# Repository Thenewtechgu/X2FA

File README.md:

# X2FA

X2FA is an open-source FIDO2 2fa key.

- What's a 2fa key

A 2FA key is a small device that adds extra security to logins by requiring both your password and the physical key. It uses secure encryption (like FIDO2 or NFC) to verify your identity and protect against hacks.

- What's FIDO2?

FIDO2 is a secure authentication standard that replaces passwords with cryptographic keys. It uses a hardware device (like a USB or NFC key) to prove your identity by signing a challenge from the website. This keeps your credentials safe and makes phishing attacks nearly impossible.

Basically, 2XFA makes it harder for hackers to hack you

Source code: Coming soon

Bill of Materials:

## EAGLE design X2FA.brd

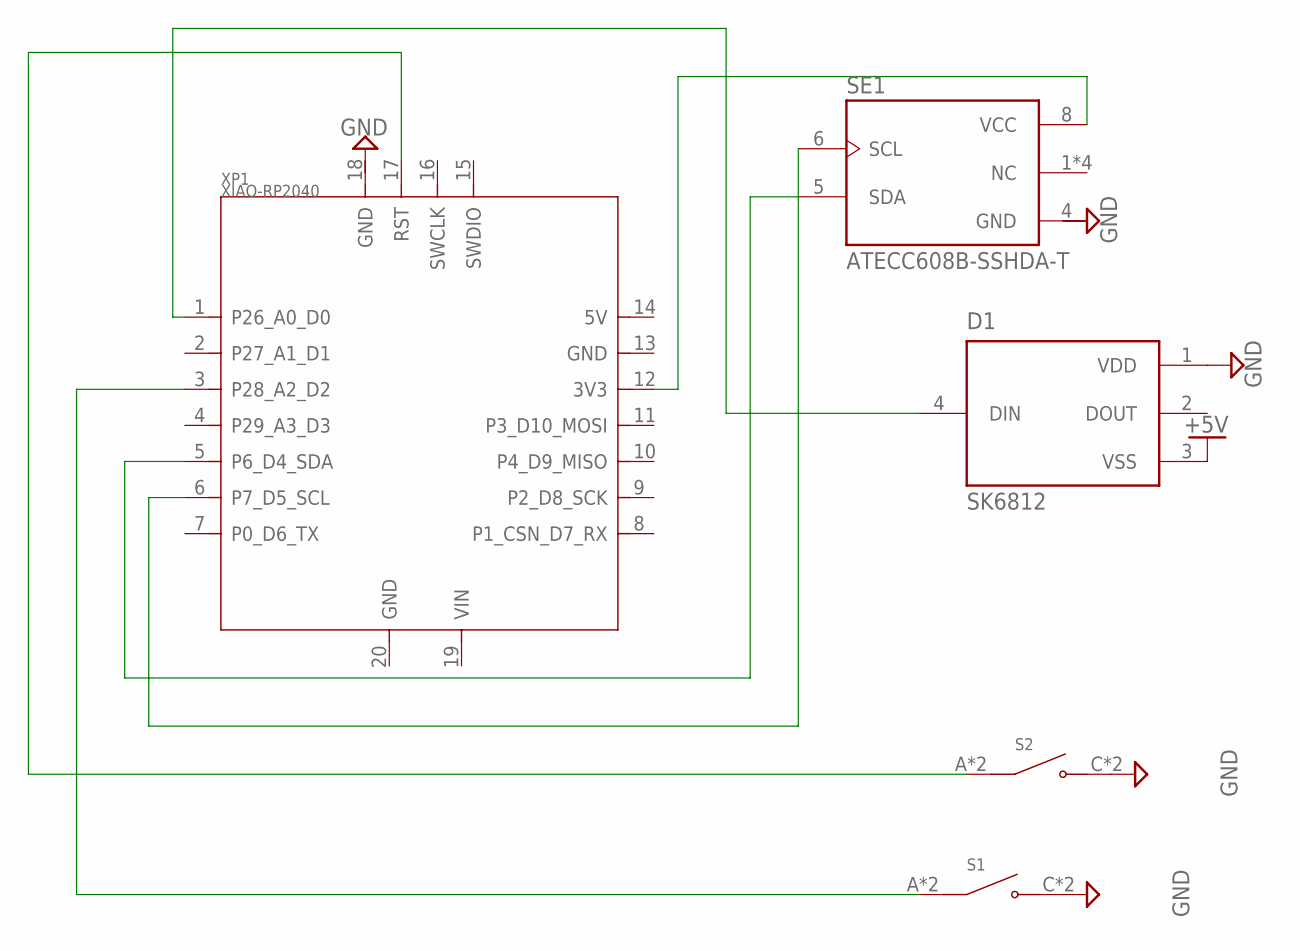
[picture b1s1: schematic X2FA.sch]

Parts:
D1: SK6812; LED_SK6812
S1, S2: TS-1187A-B-A-B; SW_TS-1187A-B-A-B
SE1: ATECC608B-SSHDA-T; SOIC127P600X175-8N
XP1: XIAO-RP2040; XIAO-SAMD21/RP2040-MODULE14P-2.54-21X17.8MM

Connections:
+5V: D1.3 (VSS)
GND: D1.1 (VDD), S1.C (NO), S1.D (NO), S2.C (NO), S2.D (NO), SE1.4 (GND)
unnamed: SE1.8 (VCC), XP1.12 (3V3)
unnamed: D1.4 (DIN), XP1.1 (P26_A0_D0)
unnamed: SE1.5 (SDA), XP1.5 (P6_D4_SDA)
unnamed: SE1.6 (SCL), XP1.6 (P7_D5_SCL)
unnamed: S2.A (COM), S2.B (COM), XP1.17 (RST)
unnamed: S1.A (COM), S1.B (COM), XP1.3 (P28_A2_D2)

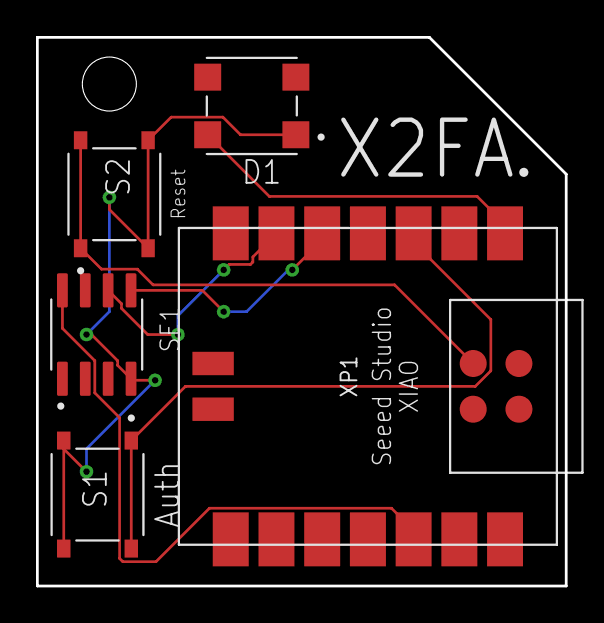
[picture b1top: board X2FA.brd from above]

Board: 2 copper layers, 29.4 x 30.5 mm, 5 parts (0 on the bottom side), 7 nets.

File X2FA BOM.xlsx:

Number | Name of part | Amount | Price per unit(USD) | Total | LCSC Part number | Designator
1 | XIAO RP2040 | 2 | 7.6 | 15.2 | C22184628 | XP1
2 | XUNPU TS-1088-AR02016 | 4 | 0.41 | 1.64 | C720477 | S1, S2
3 | MICROCHIP ATECC608B-SSHDA-T | 2 | 0.91 | 1.82 | C1518769 | SE1
4 | OPSCO Optoelectronics SK6812 | 2 | 0.42 | 0.84 | C5378720 | D1

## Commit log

2025-07-26 Added Bill of Material
2025-07-26 Added required files
2025-07-26 added brd and sch
